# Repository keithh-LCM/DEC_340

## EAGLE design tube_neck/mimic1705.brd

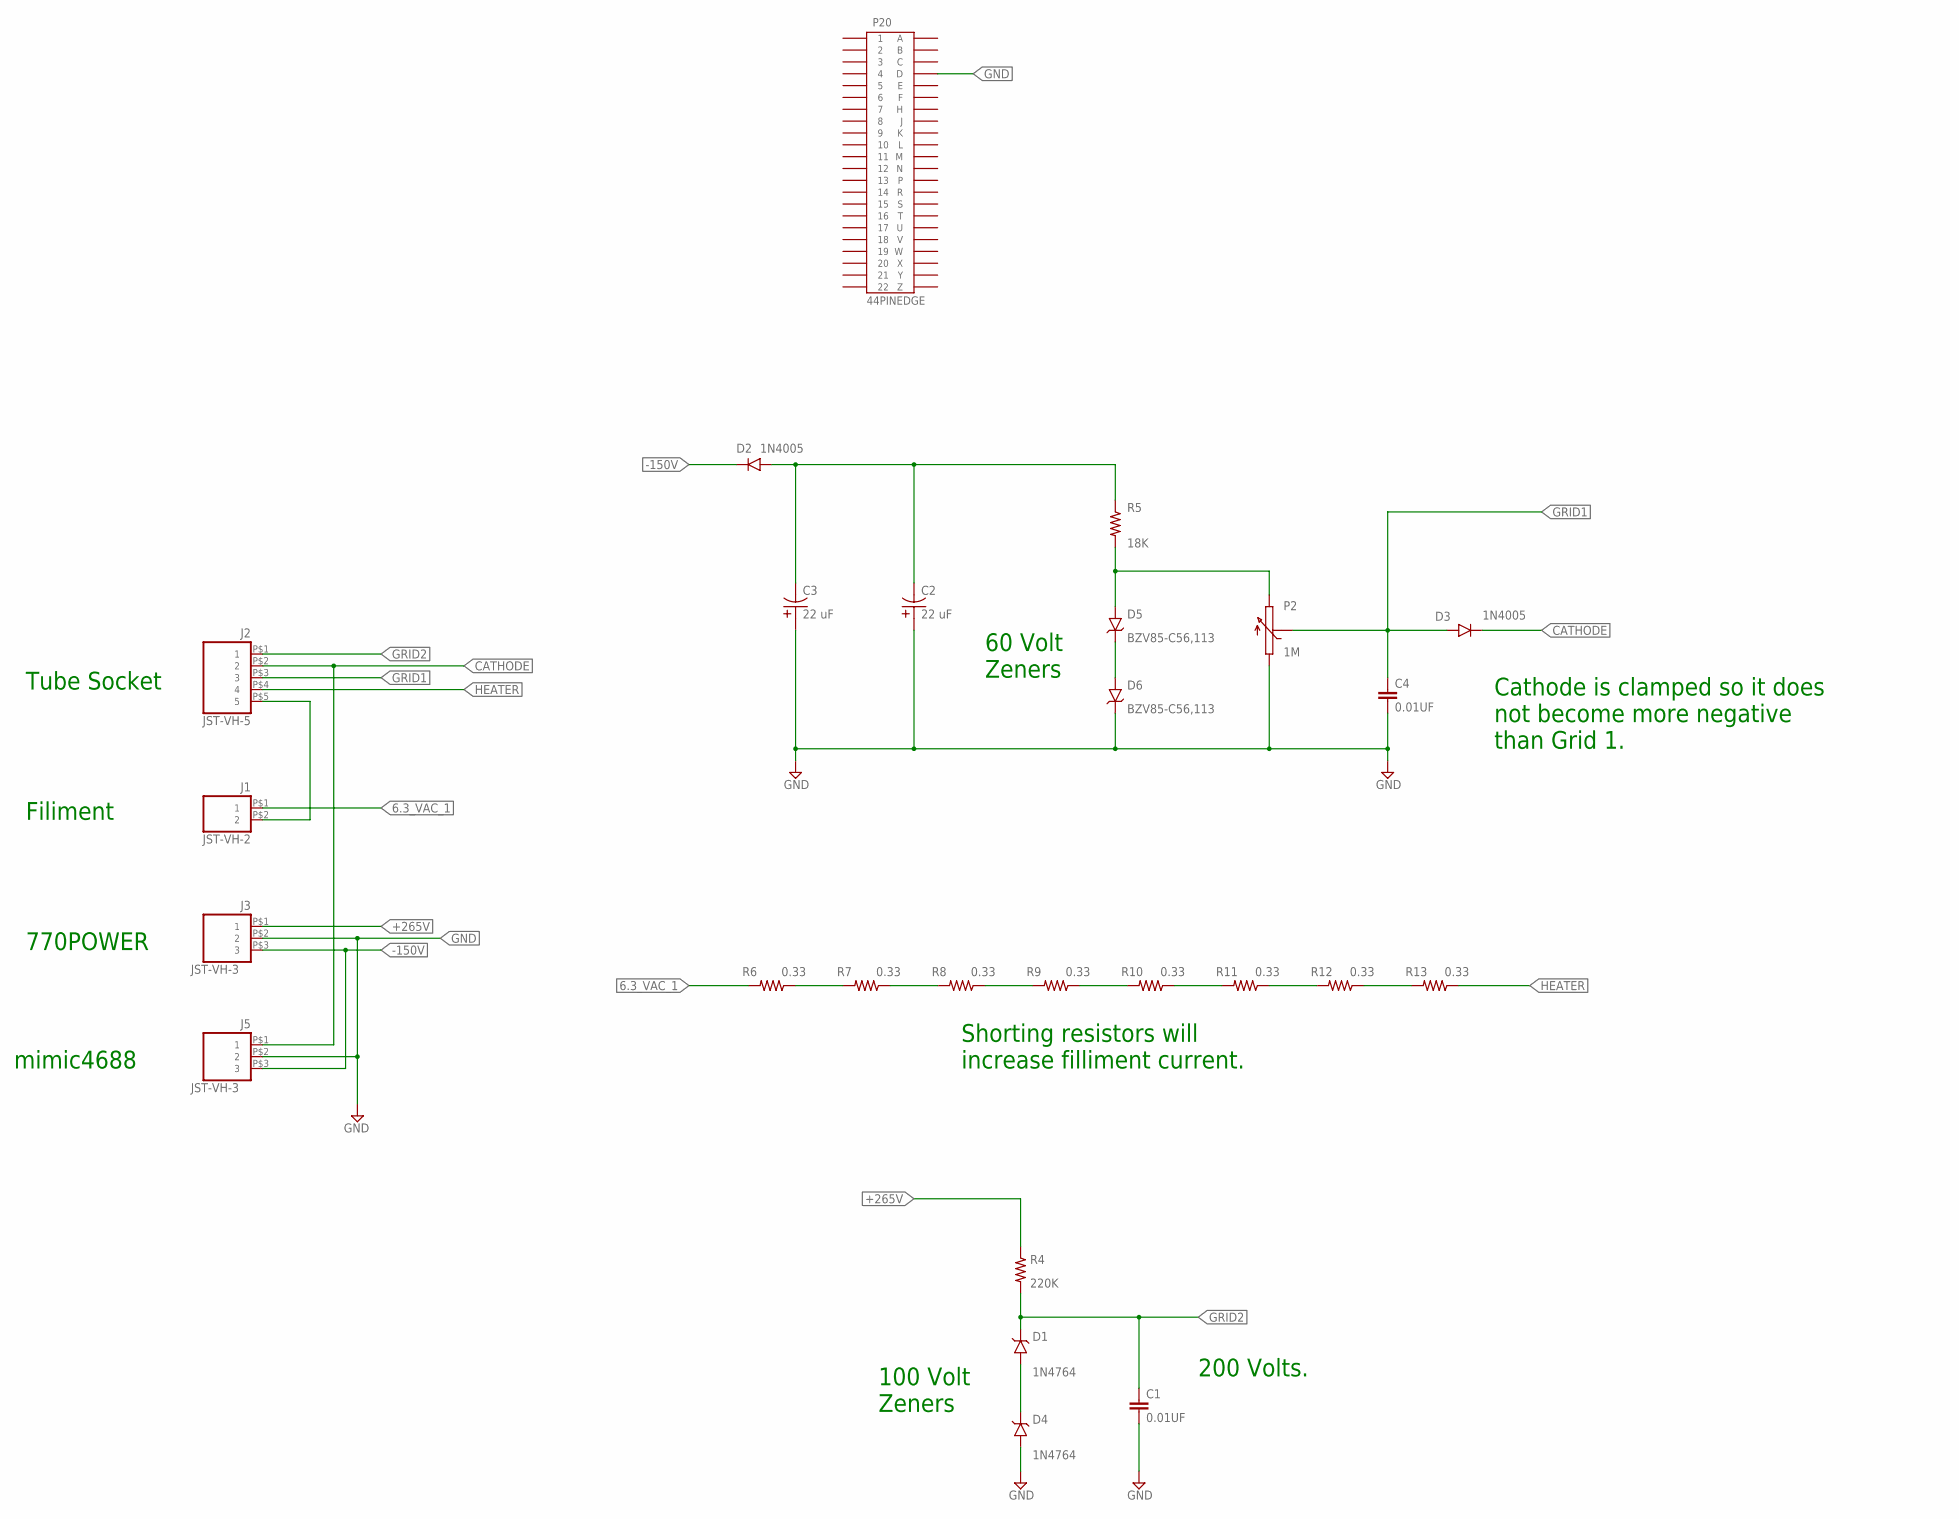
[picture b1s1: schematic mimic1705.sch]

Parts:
C1, C4: 0.01UF; 5MM_TH
C2, C3: 22 uF; AXIAL10X26
D1, D4: 1N4764; DO-41-10
D2, D3: 1N4005; DO-41-10
D5, D6: BZV85-C56,113; DO-41-10
J1: JST-VH-2; VHR-2N
J2: JST-VH-5; VHR-5N
J3, J5: JST-VH-3; VHR-3N
P2: 1M; 3006P
P20: 44PINEDGE
R4: 220K; 0207/10
R5: 18K; 0207/10
R6, R7, R8, R9, R10, R11, R12, R13: 0.33; 0309/12

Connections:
6.3_VAC_1: J1.P$1 (1), R6.2
6.3_VAC_2: J1.P$2 (2), J2.P$5 (5)
+265V: J3.P$1 (1), R4.1
-150V: D2.C, J3.P$3 (3), J5.P$3 (3)
CATHODE: D3.C, J2.P$2 (2), J5.P$1 (1)
GND: C1.2, C2.P$1 (1), C3.P$1 (1), C4.2, D4.A, D6.C, J3.P$2 (2), J5.P$2 (2), P2.1, P20.D
GRID1: C4.1, D3.A, J2.P$3 (3), P2.2
GRID2: C1.1, D1.C, J2.P$1 (1), R4.2
HEATER: J2.P$4 (4), R13.1
unnamed: D5.C, D6.A
unnamed: D1.A, D4.C
unnamed: R6.1, R7.2
unnamed: D5.A, P2.3, R5.2
unnamed: C2.P$2 (2), C3.P$2 (2), D2.A, R5.1
unnamed: R7.1, R8.2
unnamed: R8.1, R9.2
unnamed: R9.1, R10.2
unnamed: R10.1, R11.2
unnamed: R11.1, R12.2
unnamed: R12.1, R13.2

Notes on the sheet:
770POWER
Tube Socket
Cathode is clamped so it does not become more negative than Grid 1.
200 Volts.
Shorting resistors will increase filliment current.
mimic4688
Filiment
100 Volt Zeners
60 Volt Zeners

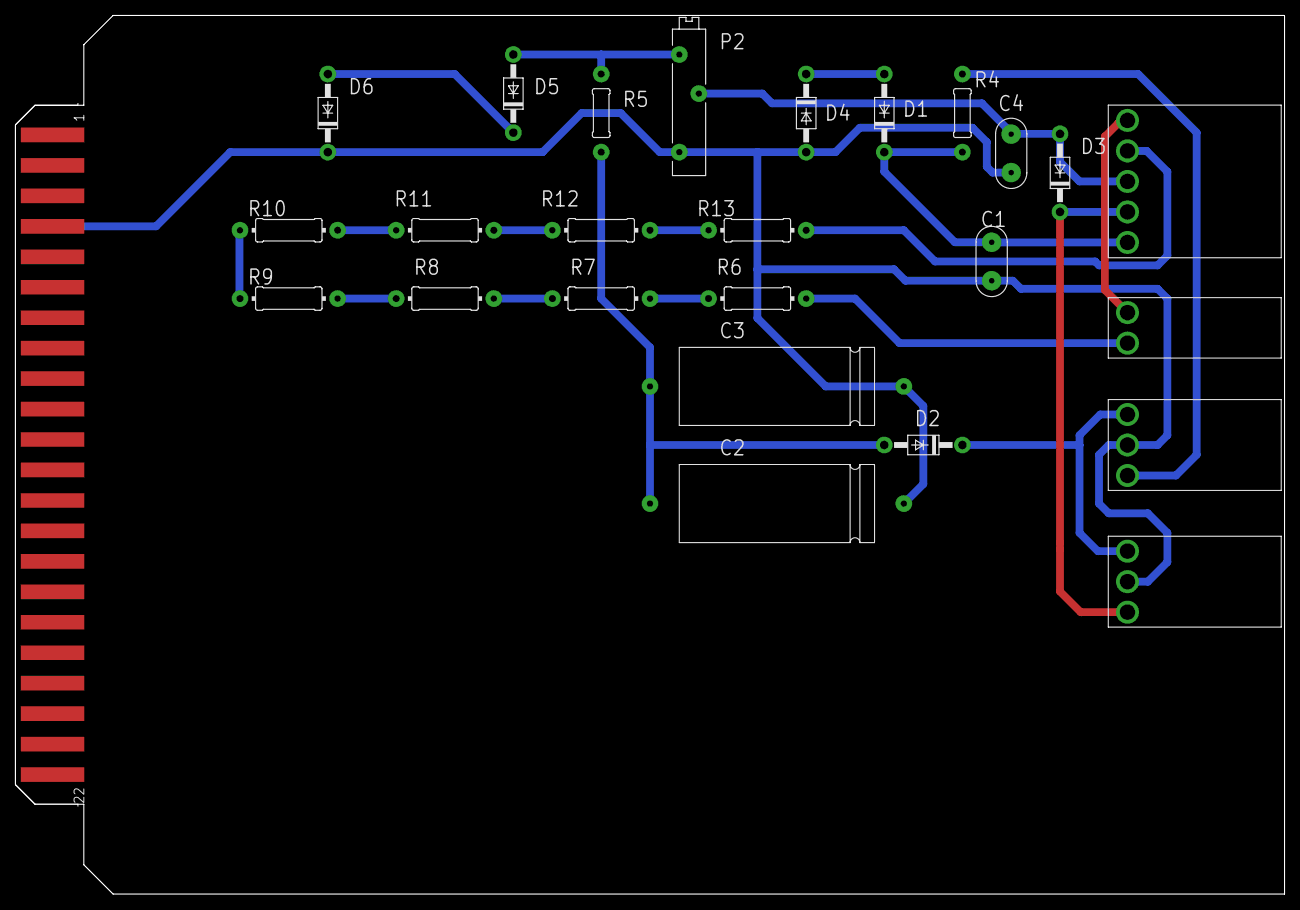
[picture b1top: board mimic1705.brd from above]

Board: 2 copper layers, 165.1 x 114.3 mm, 26 parts (0 on the bottom side), 20 nets.

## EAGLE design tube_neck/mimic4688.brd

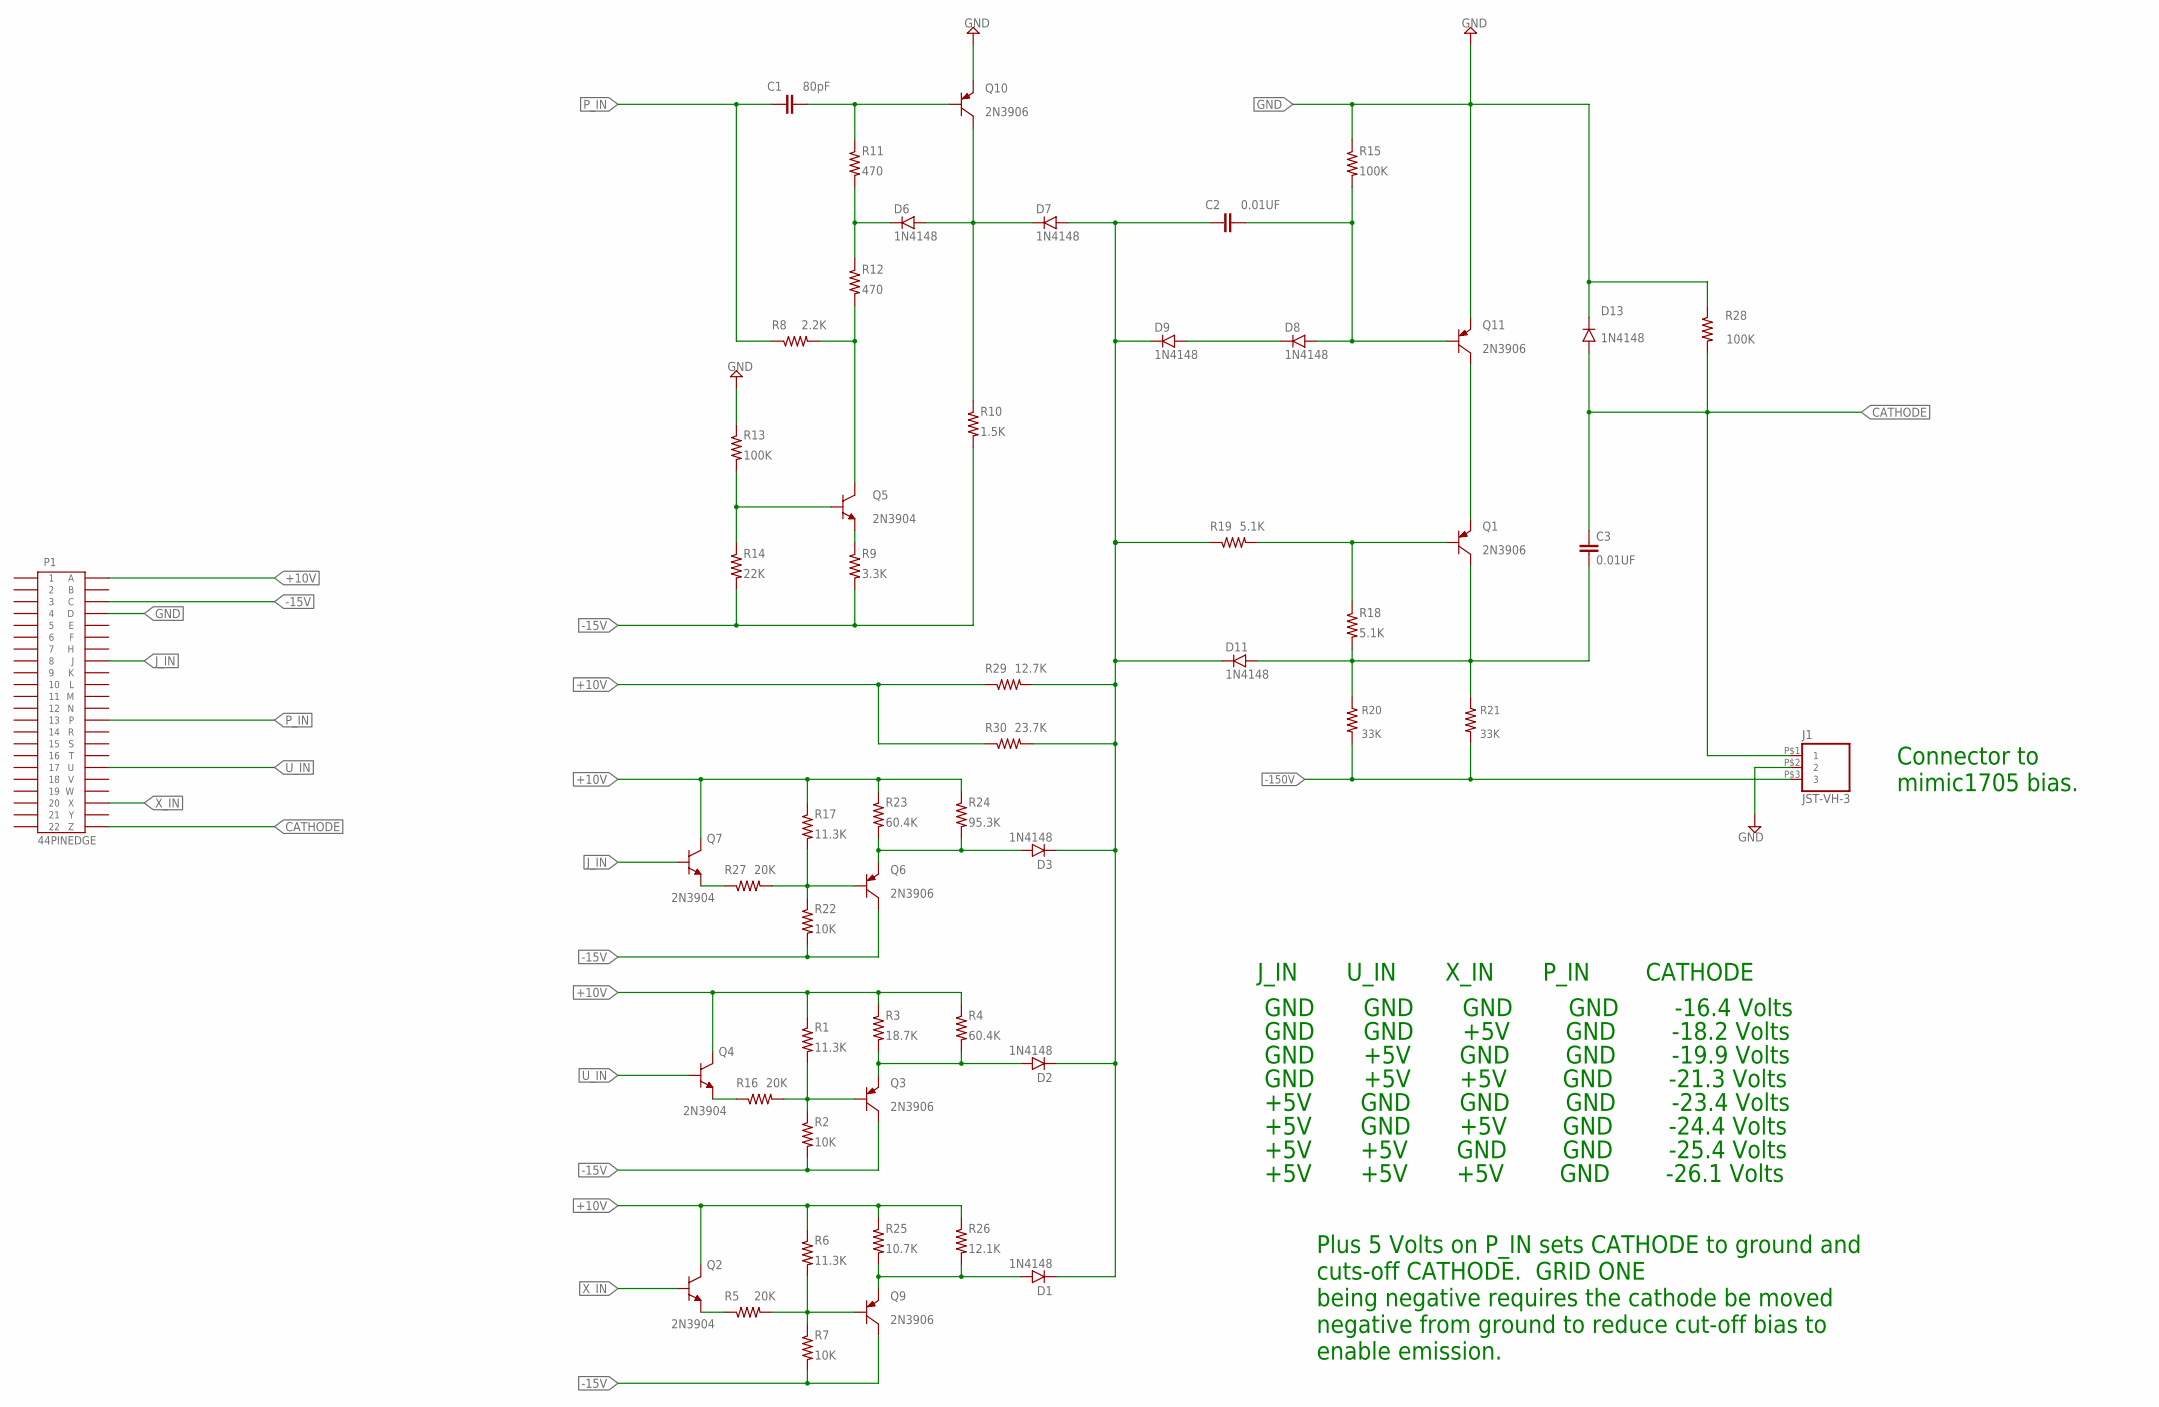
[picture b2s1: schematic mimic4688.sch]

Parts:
C1: 80pF; 5MM_TH
C2, C3: 0.01UF; 5MM_TH
D1, D2, D3, D6, D7, D8, D9, D11, D13: 1N4148; DO35-7
J1: JST-VH-3; VHR-3N
P1: 44PINEDGE
Q1, Q3, Q6, Q9, Q10, Q11: 2N3906; TO92
Q2, Q4, Q5, Q7: 2N3904; TO92
R1, R6, R17: 11.3K; 0207/10
R2, R7, R22: 10K; 0207/10
R3: 18.7K; 0207/10
R4, R23: 60.4K; 0207/10
R5, R16, R27: 20K; 0207/10
R8: 2.2K; 0207/10
R9: 3.3K; 0207/10
R10: 1.5K; 0207/10
R11, R12: 470; 0207/10
R13, R15, R28: 100K; 0207/10
R14: 22K; 0207/10
R18, R19: 5.1K; 0207/10
R20, R21: 33K; RR02
R24: 95.3K; 0207/10
R25: 10.7K; 0207/10
R26: 12.1K; 0207/10
R29: 12.7K; 0207/10
R30: 23.7K; 0207/10

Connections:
+10V: P1.A, Q2.3 (C), Q4.3 (C), Q7.3 (C), R1.1, R3.1, R4.1, R6.1, R17.1, R23.1, R24.1, R25.1, R26.1, R29.1, R30.1
-15V: P1.C, Q3.1 (C), Q6.1 (C), Q9.1 (C), R2.2, R7.2, R9.2, R10.2, R14.2, R22.2
-150V: J1.P$3 (3), R20.2, R21.2
CATHODE: C3.1, D13.A, J1.P$1 (1), P1.Z, R28.2
GND: D13.C, J1.P$2 (2), P1.D, Q10.3 (E), Q11.3 (E), R13.1, R15.1, R28.1
J_IN: P1.J, Q7.2 (B)
unnamed: C1.2, Q10.2 (B), R11.1
unnamed: Q3.2 (B), R1.2, R2.1, R16.2
unnamed: D2.A, Q3.3 (E), R3.2, R4.2
unnamed: Q9.2 (B), R5.2, R6.2, R7.1
unnamed: Q2.1 (E), R5.1
unnamed: D6.A, D7.C, Q10.1 (C), R10.1
unnamed: D6.C, R11.2, R12.1
unnamed: Q5.3 (C), R8.2, R12.2
unnamed: Q4.1 (E), R16.1
unnamed: Q5.1 (E), R9.1
unnamed: Q5.2 (B), R13.2, R14.1
unnamed: Q6.2 (B), R17.2, R22.1, R27.2
unnamed: D8.C, D9.A
unnamed: Q1.3 (E), Q11.1 (C)
unnamed: D3.A, Q6.3 (E), R23.2, R24.2
unnamed: D1.A, Q9.3 (E), R25.2, R26.2
unnamed: Q1.2 (B), R18.1, R19.2
unnamed: C2.2, D8.A, Q11.2 (B), R15.2
unnamed: C2.1, D1.C, D2.C, D3.C, D7.A, D9.C, D11.C, R19.1, R29.2, R30.2
unnamed: Q7.1 (E), R27.1
P_IN: C1.1, P1.P, R8.1
U_IN: P1.U, Q4.2 (B)
X_IN: P1.X, Q2.2 (B)
Y_OUT: C3.2, D11.A, Q1.1 (C), R18.2, R20.1, R21.1

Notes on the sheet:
Plus 5 Volts on P_IN sets CATHODE to ground and cuts-off CATHODE. GRID ONE being negative requires the cathode be moved negative from ground to reduce cut-off bias to enable emission.
J_IN U_IN X_IN P_IN CATHODE
GND GND GND GND -16.4 Volts
GND GND +5V GND -18.2 Volts
GND +5V GND GND -19.9 Volts
GND +5V +5V GND -21.3 Volts
+5V GND GND GND -23.4 Volts
+5V GND +5V GND -24.4 Volts
+5V +5V GND GND -25.4 Volts
+5V +5V +5V GND -26.1 Volts
Connector to mimic1705 bias.

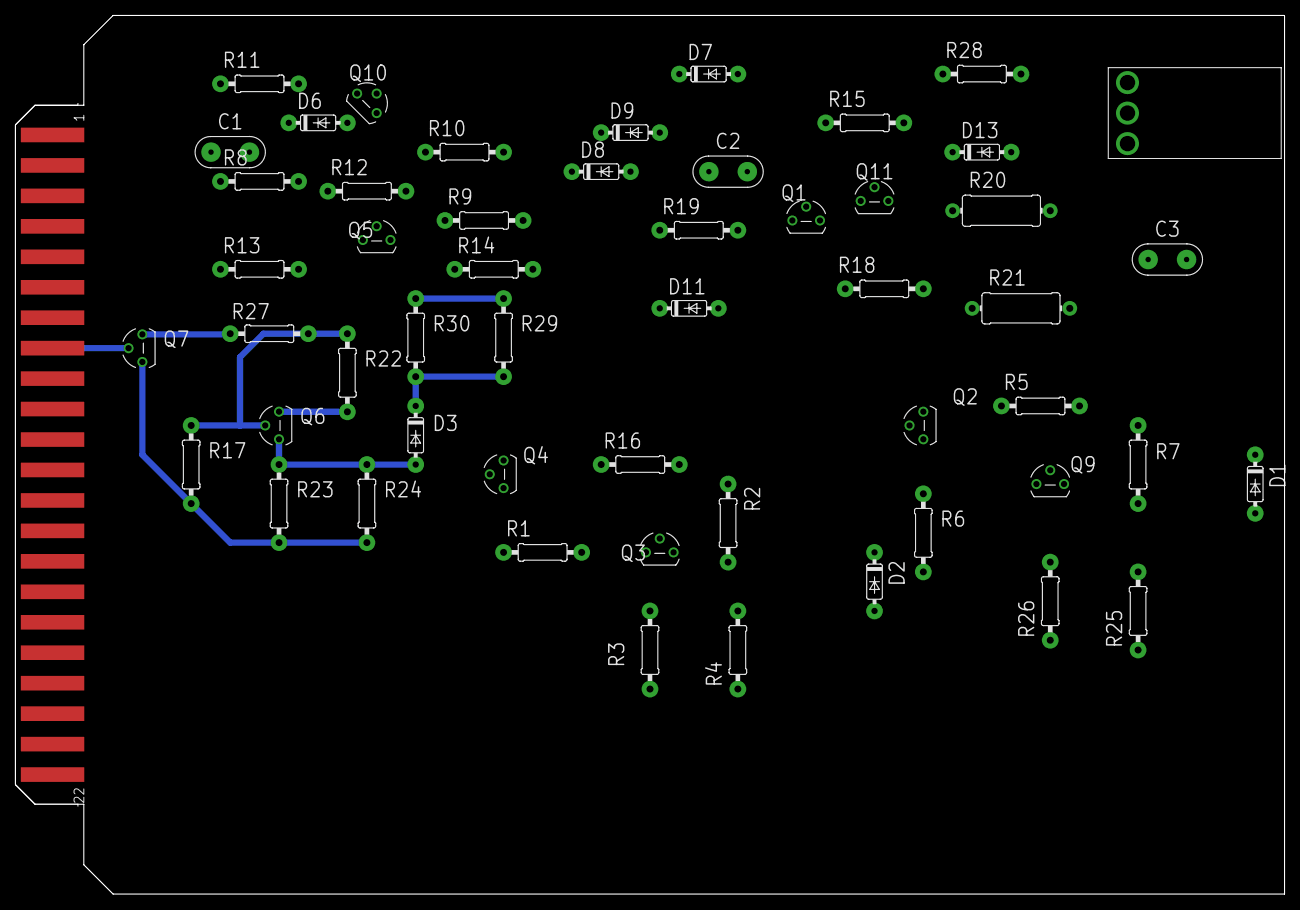
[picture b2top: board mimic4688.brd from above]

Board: 2 copper layers, 165.1 x 114.3 mm, 54 parts (0 on the bottom side), 30 nets.

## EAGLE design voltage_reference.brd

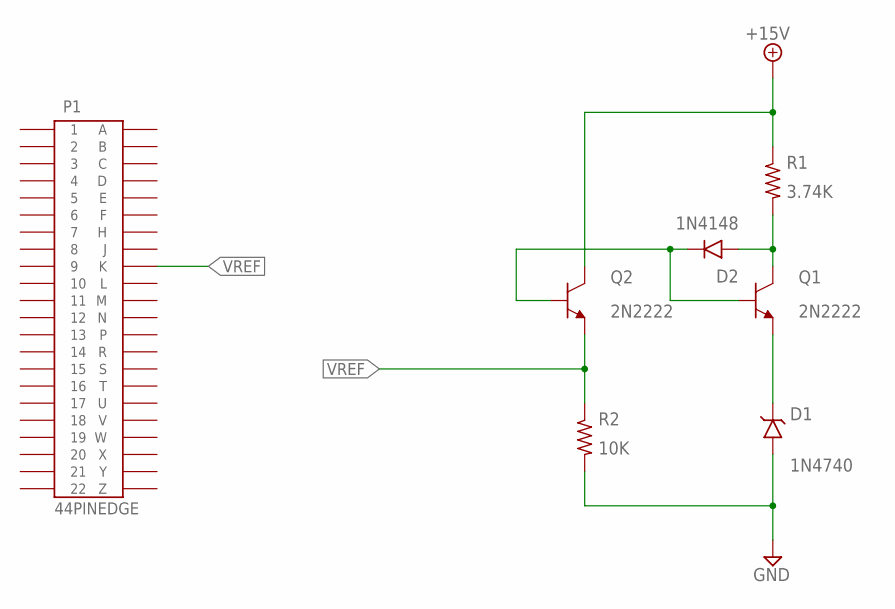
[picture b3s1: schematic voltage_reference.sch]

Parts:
D1: 1N4740; DO41
D2: 1N4148; DO35-7
P1: 44PINEDGE
Q1, Q2: 2N2222; TO18
R1: 3.74K; 0207/10
R2: 10K; 0207/10

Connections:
+15V: Q2.3 (C), R1.1
GND: D1.A, R2.2
unnamed: D1.C, Q1.1 (E)
unnamed: D2.A, Q1.3 (C), R1.2
unnamed: D2.C, Q1.2 (B), Q2.2 (B)
VREF: P1.K, Q2.1 (E), R2.1

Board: 2 copper layers, 7 parts (0 on the bottom side), 6 nets, no tracks yet.

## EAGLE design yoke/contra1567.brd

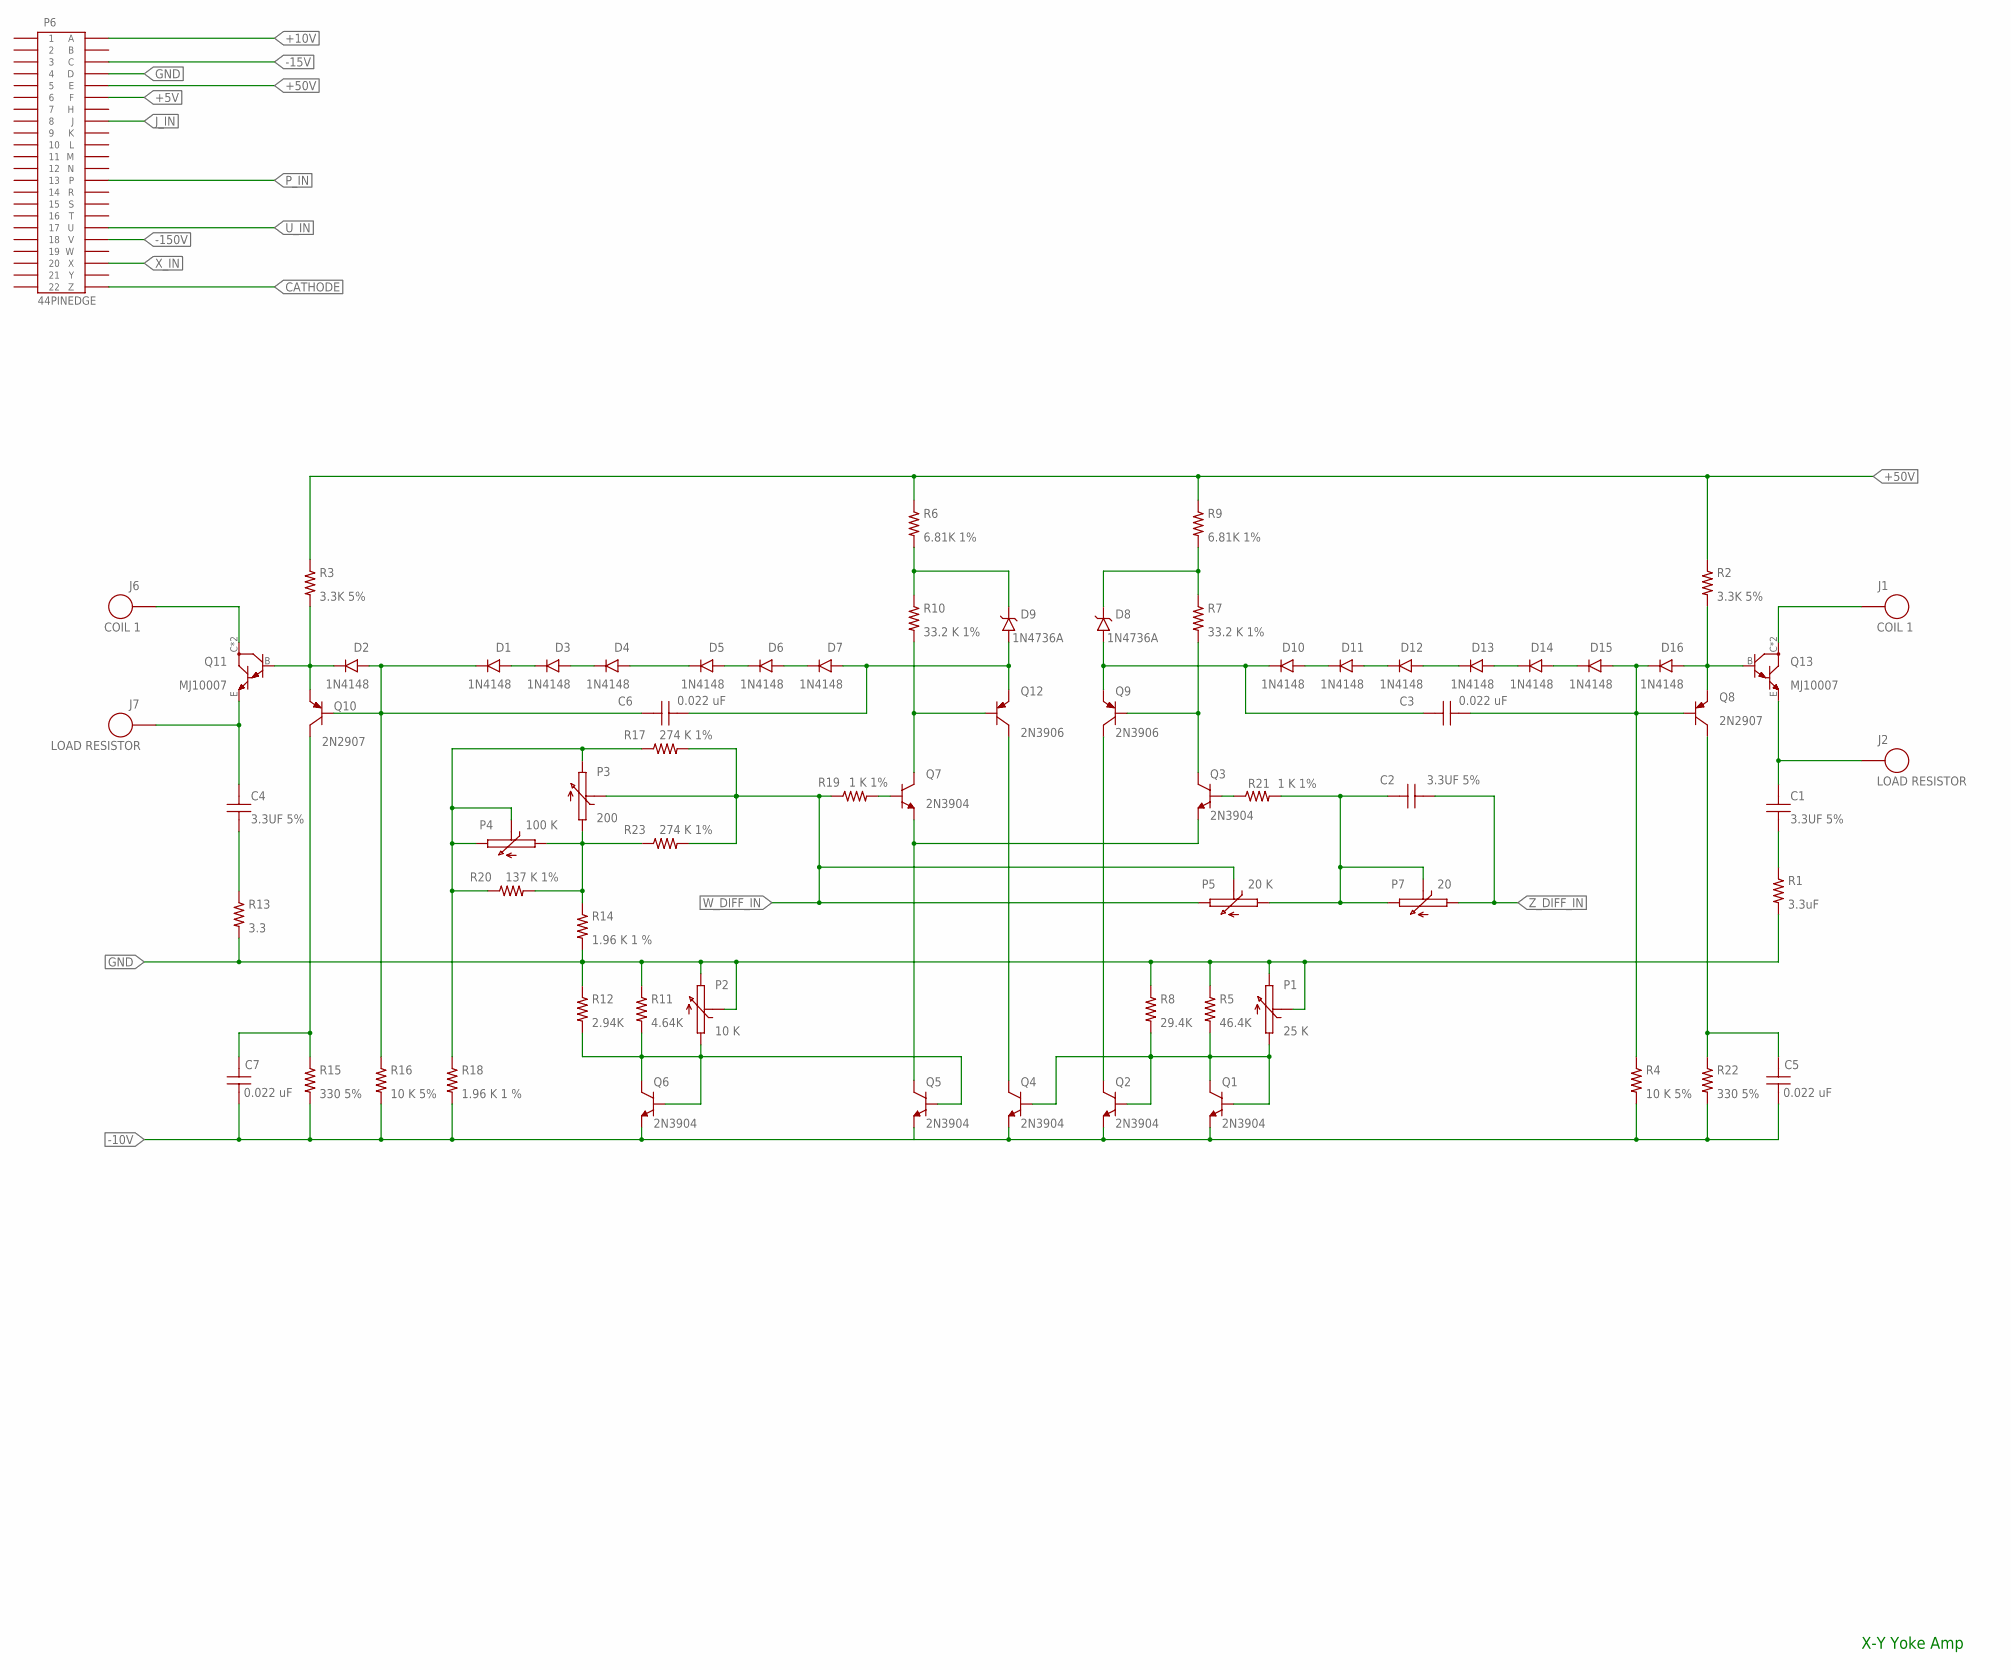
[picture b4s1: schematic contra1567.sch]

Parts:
C1, C2, C4: 3.3UF 5%; CAP-3-PT-ZERO-3UF-250V-FILM
C3, C5, C6, C7: 0.022 uF; CAP-ZERO-PT-ZERO-22UF-250V-FILM
D1, D2, D3, D4, D5, D6, D7, D10, D11, D12, D13, D14, D15, D16: 1N4148; DO35-7
D8, D9: 1N4736A; DO41
J1, J6: COIL 1; AWG18
J2, J7: LOAD RESISTOR; AWG18
P1: 25 K; 3006P
P2: 10 K; 3006P
P3: 200; 3006P
P4: 100 K; 3006P
P5: 20 K; 3006P
P6: 44PINEDGE
P7: 20; 3006P
Q1, Q2, Q3, Q4, Q5, Q6, Q7: 2N3904; TO92
Q8, Q10: 2N2907; TO18
Q9, Q12: 2N3906; TO92
Q11, Q13: MJ10007; TO3
R1: 3.3uF; R_THREEWATT
R2, R3: 3.3K 5%; R_TWOWATT
R4, R16: 10 K 5%; R_HALFWATT
R5: 46.4K; R_QUARTERWATT
R6, R9: 6.81K 1%; R_HALFWATT
R7, R10: 33.2 K 1%; R_HALFWATT
R8: 29.4K; R_QUARTERWATT
R11: 4.64K; R_QUARTERWATT
R12: 2.94K; R_QUARTERWATT
R13: 3.3; R_THREEWATT
R14, R18: 1.96 K 1 %; R_QUARTERWATT
R15, R22: 330 5%; R_ONEWATT
R17, R23: 274 K 1%; R_QUARTERWATT
R19, R21: 1 K 1%; R_QUARTERWATT
R20: 137 K 1%; R_QUARTERWATT

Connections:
+5V: P6.F
+10V: P6.A
+50V: P6.E, R2.1, R3.1, R6.1, R9.1
-10V: C5.1, C7.1, Q1.3 (E), Q2.3 (E), Q4.3 (E), Q6.3 (E), R4.2, R15.2, R16.2, R18.2, R22.2
-15V: P6.C
-150V: P6.V
CATHODE: P6.Z
GND: P1.2 (S), P1.3 (E), P2.2 (S), P2.3 (E), P6.D, R1.2, R5.1, R8.1, R11.1, R12.1, R13.2, R14.2
J_IN: P6.J
unnamed: J1.P$1, Q13.C, Q13.C/ (C)
unnamed: C1.1, J2.P$1, Q13.E
unnamed: C1.2, R1.1
unnamed: P1.1 (A), Q1.1 (C), Q1.2 (B), Q2.2 (B), Q4.2 (B), R5.2, R8.2
unnamed: D16.A, Q8.1 (E), Q13.B, R2.2
unnamed: Q3.2 (B), R21.1
unnamed: C3.2, D15.A, D16.C, Q8.2 (B), R4.1
unnamed: C5.2, Q8.3 (C), R22.1
unnamed: Q4.1 (C), Q12.1 (C)
unnamed: D14.A, D15.C
unnamed: D13.A, D14.C
unnamed: D12.A, D13.C
unnamed: D11.A, D12.C
unnamed: D10.A, D11.C
unnamed: C3.1, D8.A, D10.C, Q9.3 (E)
unnamed: Q3.1 (C), Q9.2 (B), R7.2
unnamed: D8.C, R7.1, R9.2
unnamed: C2.1, P5.1 (A), P7.2 (S), P7.3 (E), R21.2
unnamed: Q3.3 (E), Q5.1 (C), Q7.3 (E)
unnamed: D9.C, R6.2, R10.1
unnamed: Q2.1 (C), Q9.1 (C)
unnamed: P3.1 (A), P4.1 (A), R14.1, R20.2, R23.1
unnamed: Q7.1 (C), Q12.2 (B), R10.2
unnamed: J6.P$1, Q11.C, Q11.C/ (C)
unnamed: C4.1, J7.P$1, Q11.E
unnamed: P2.1 (A), Q5.2 (B), Q6.1 (C), Q6.2 (B), R11.2, R12.2
unnamed: C4.2, R13.1
unnamed: D2.C, Q10.1 (E), Q11.B, R3.2
unnamed: C6.1, D1.C, D2.A, Q10.2 (B), R16.1
unnamed: C7.2, Q10.3 (C), R15.1
unnamed: D1.A, D3.C
unnamed: D3.A, D4.C
unnamed: D4.A, D5.C
unnamed: D5.A, D6.C
unnamed: D6.A, D7.C
unnamed: C6.2, D7.A, D9.A, Q12.3 (E)
unnamed: Q7.2 (B), R19.2
unnamed: P3.3 (E), P4.2 (S), P4.3 (E), R17.1, R18.1, R20.1
P_IN: P6.P
U_IN: P6.U
W_DIFF_IN: P3.2 (S), P5.2 (S), P5.3 (E), R17.2, R19.1, R23.2
X_IN: P6.X
Z_DIFF_IN: C2.2, P7.1 (A)

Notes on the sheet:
X-Y Yoke Amp

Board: 2 copper layers, 70 parts (0 on the bottom side), 43 nets, no tracks yet.

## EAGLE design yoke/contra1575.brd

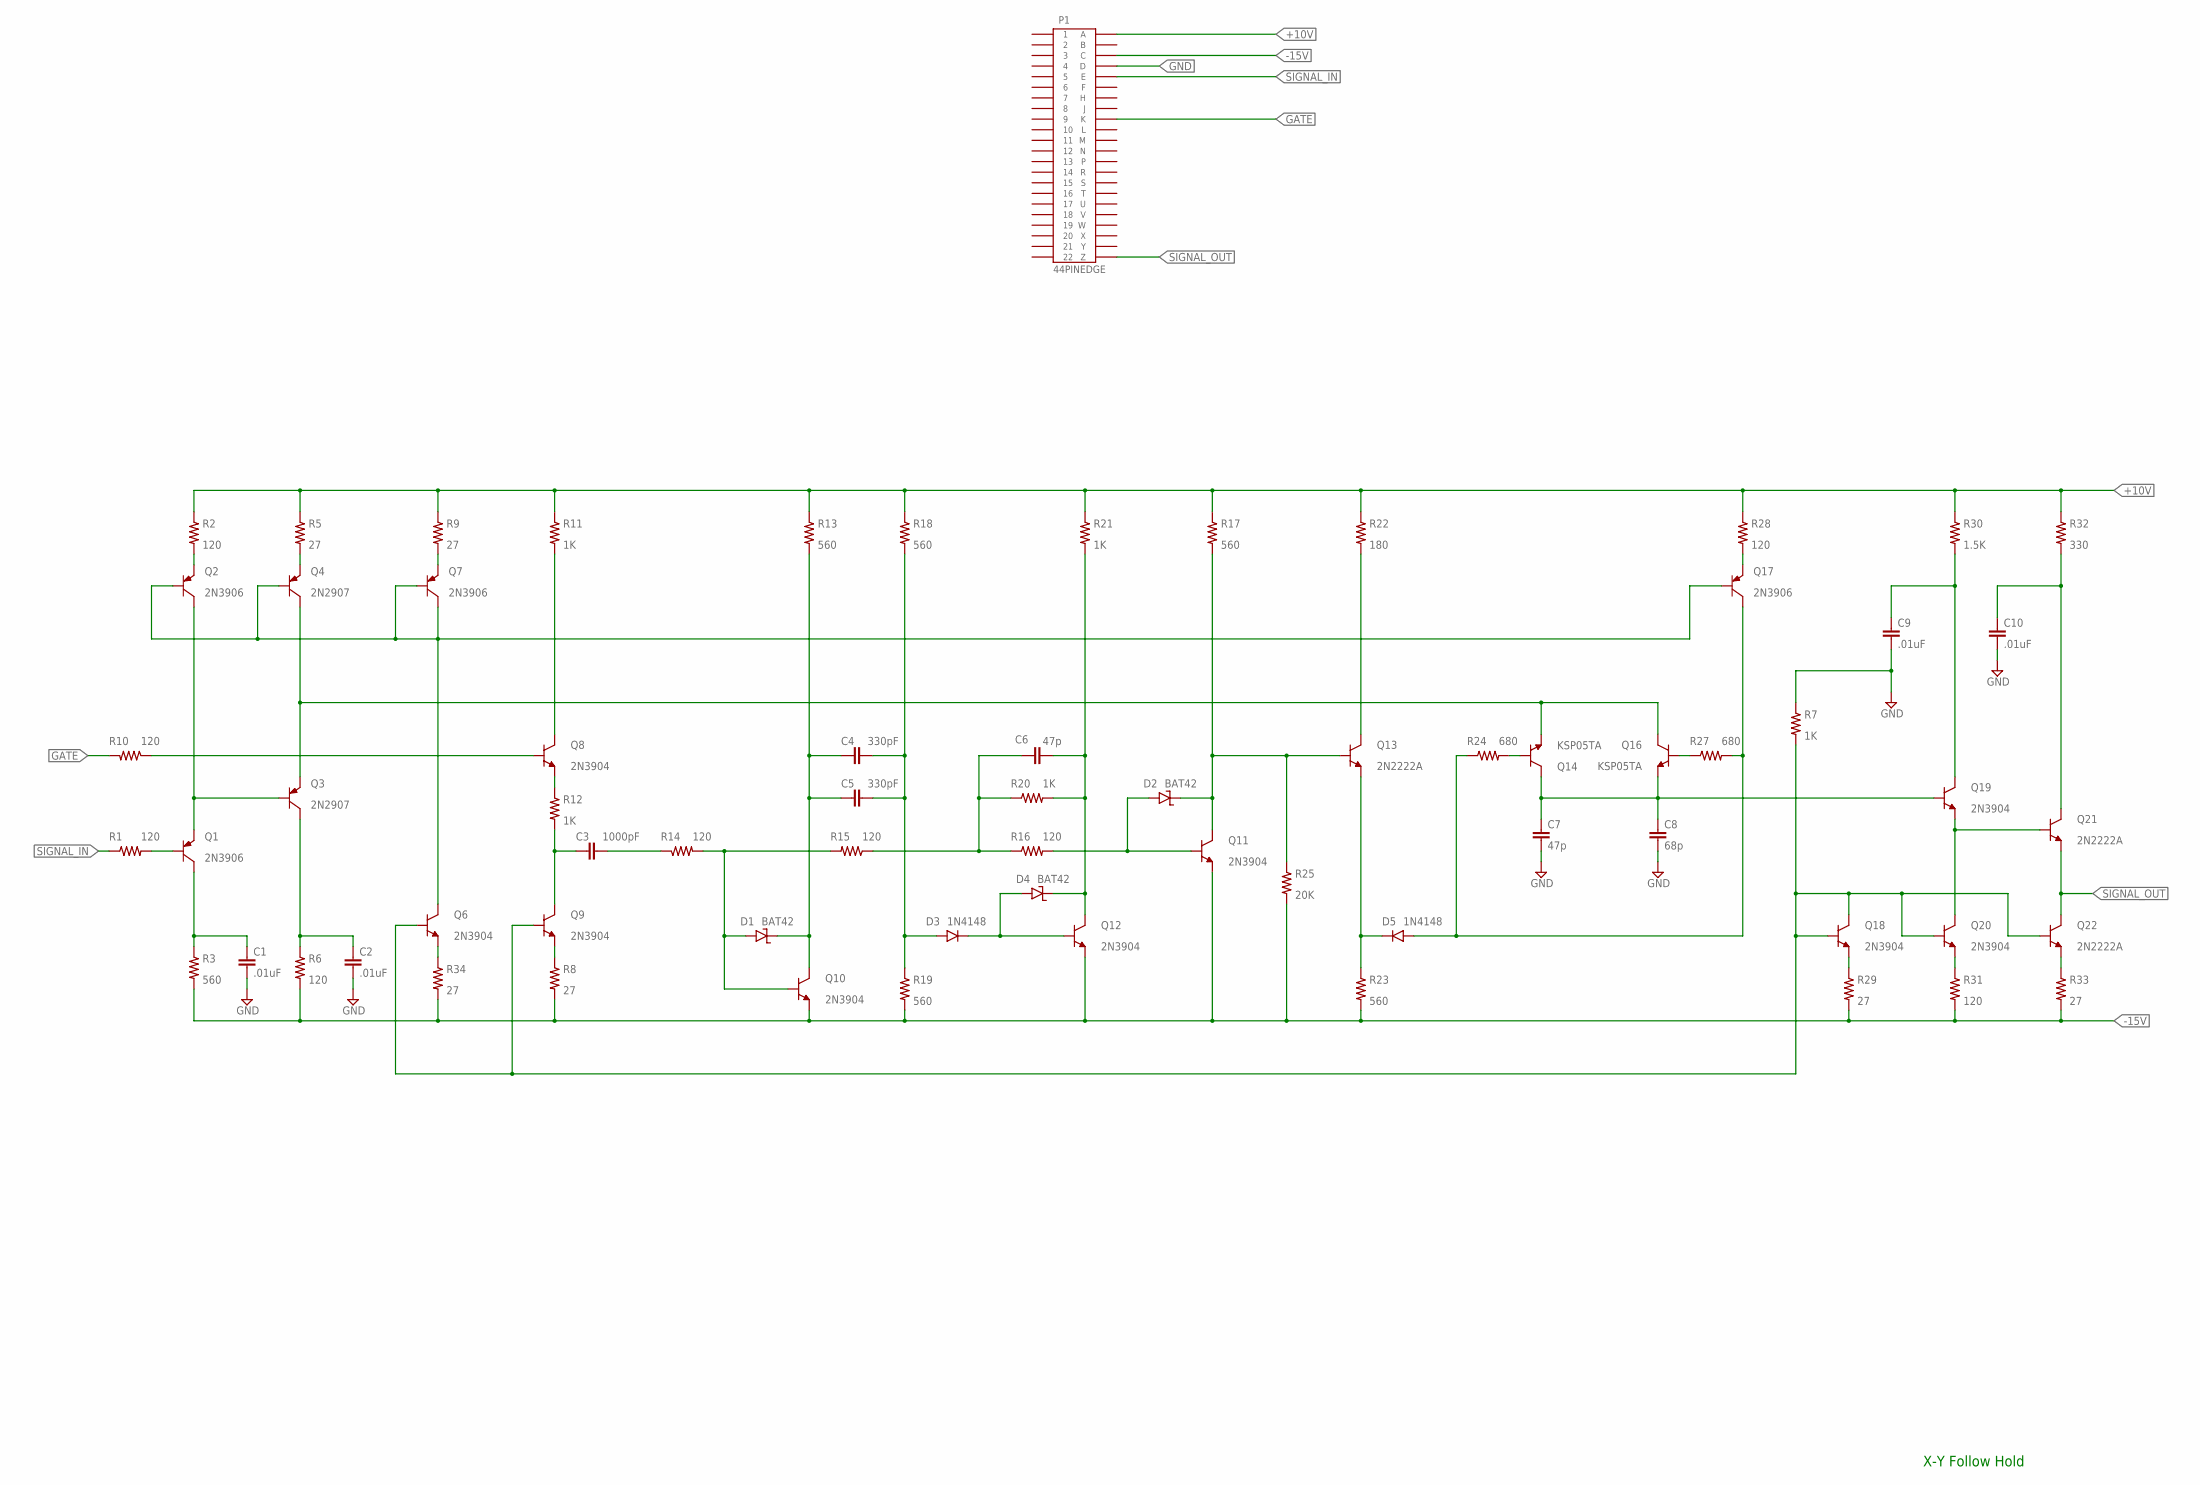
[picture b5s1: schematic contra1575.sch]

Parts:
C1, C2, C9, C10: .01uF; 5MM_TH
C3: 1000pF; 5MM_TH
C4, C5: 330pF; 5MM_TH
C6, C7: 47p; 5MM_TH
C8: 68p; 5MM_TH
D1, D2, D4: BAT42; DO35-7
D3, D5: 1N4148; DO35-7
P1: 44PINEDGE
Q1, Q2, Q7, Q17: 2N3906; TO92
Q3, Q4: 2N2907; TO18
Q6, Q8, Q9, Q10, Q11, Q12, Q18, Q19, Q20: 2N3904; TO92
Q13, Q21, Q22: 2N2222A; TO18
Q14, Q16: KSP05TA; TO92
R1, R2, R6, R10, R14, R15, R16, R28, R31: 120; R_QUARTERWATT
R3: 560; R_QUARTERWATT
R5, R8, R9, R29, R33, R34: 27; R_QUARTERWATT
R7: 1K; R_HALFWATT
R11, R20, R21: 1K; R_ONEWATT
R12: 1K; R_QUARTERWATT
R13, R17, R23: 560; R_TWOWATT
R18, R19: 560; R_ONEWATT
R22: 180; R_HALFWATT
R24, R27: 680; R_QUARTERWATT
R25: 20K; R_QUARTERWATT
R30: 1.5K; R_QUARTERWATT
R32: 330; R_QUARTERWATT

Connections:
+10V: P1.A, R2.1, R5.1, R9.1, R11.1, R13.1, R17.1, R18.1, R21.1, R22.1, R28.1, R30.1, R32.1
-15V: P1.C, Q10.1 (E), Q11.1 (E), Q12.1 (E), R3.2, R6.2, R8.2, R19.2, R23.2, R25.2, R29.2, R31.2, R33.2, R34.2
GATE: P1.K, R10.2
GND: C1.2, C2.2, C7.2, C8.2, C9.2, C10.2, P1.D, R7.1
unnamed: D3.C, D4.A, Q12.2 (B)
unnamed: C4.2, C5.2, D3.A, R18.2, R19.1
unnamed: Q9.1 (E), R8.1
unnamed: Q13.3 (C), R22.2
unnamed: C6.2, R15.1, R16.1, R20.1
unnamed: Q3.1 (E), Q4.3 (C), Q14.1 (E), Q16.3 (C)
unnamed: C7.1, C8.1, Q14.3 (C), Q16.1 (E), Q19.2 (B)
unnamed: C6.1, D4.C, Q12.3 (C), R20.2, R21.2
unnamed: Q14.2 (B), R24.2
unnamed: Q16.2 (B), R27.1
unnamed: D5.A, Q17.1 (C), R24.1, R27.2
unnamed: Q17.3 (E), R28.2
unnamed: Q2.2 (B), Q4.2 (B), Q6.3 (C), Q7.1 (C), Q7.2 (B), Q17.2 (B)
unnamed: D2.A, Q11.2 (B), R16.2
unnamed: D5.C, Q13.1 (E), R23.1
unnamed: Q19.1 (E), Q20.3 (C), Q21.2 (B)
unnamed: Q6.1 (E), R34.1
unnamed: C10.1, Q21.3 (C), R32.2
unnamed: C9.1, Q19.3 (C), R30.2
unnamed: D2.C, Q11.3 (C), Q13.2 (B), R17.2, R25.1
unnamed: Q22.1 (E), R33.1
unnamed: Q20.1 (E), R31.1
unnamed: Q18.1 (E), R29.1
unnamed: C3.2, R14.1
unnamed: D1.A, Q10.2 (B), R14.2, R15.2
unnamed: C4.1, C5.1, D1.C, Q10.3 (C), R13.2
unnamed: C3.1, Q9.3 (C), R12.2
unnamed: Q7.3 (E), R9.2
unnamed: Q8.1 (E), R12.1
unnamed: C1.1, Q1.1 (C), R3.1
unnamed: Q6.2 (B), Q9.2 (B), Q18.2 (B), Q18.3 (C), Q20.2 (B), Q22.2 (B), R7.2
unnamed: Q8.2 (B), R10.1
unnamed: Q8.3 (C), R11.2
unnamed: C2.1, Q3.3 (C), R6.1
unnamed: Q4.1 (E), R5.2
unnamed: Q1.3 (E), Q2.1 (C), Q3.2 (B)
unnamed: Q2.3 (E), R2.2
unnamed: Q1.2 (B), R1.2
SIGNAL_IN: P1.E, R1.1
SIGNAL_OUT: P1.Z, Q21.1 (E), Q22.3 (C)

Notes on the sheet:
X-Y Follow Hold

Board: 2 copper layers, 68 parts (0 on the bottom side), 44 nets, no tracks yet.
